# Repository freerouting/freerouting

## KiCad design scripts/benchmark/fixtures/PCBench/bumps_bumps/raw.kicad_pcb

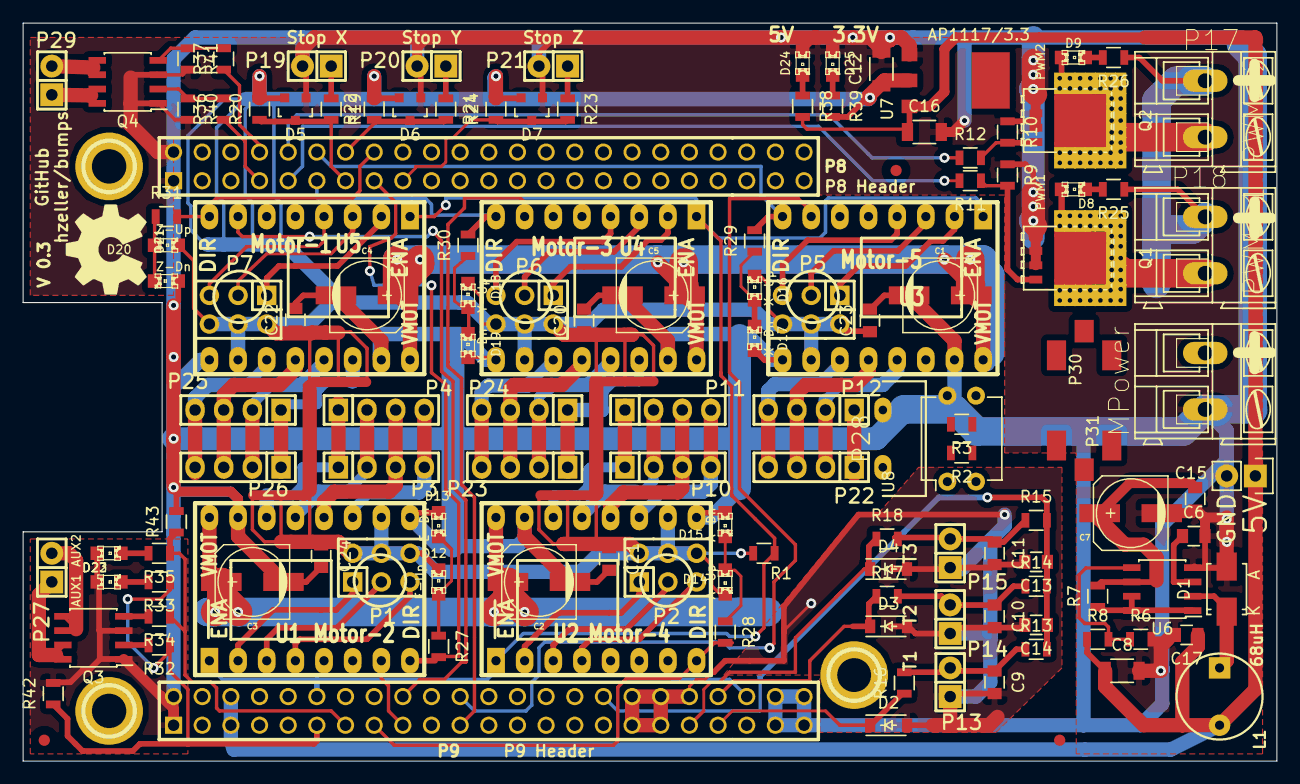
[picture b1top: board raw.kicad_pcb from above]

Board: 2 copper layers, 111.1 x 65.4 mm, 134 parts (0 on the bottom side), 101 nets.

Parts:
C1, C2, C3, C4, C5, C7: 100u; c_elec_6.3x7.7
C6: 110p; C_0805
C8: 100u; C_1206
C9, C10, C11, C14: 10u; C_0805
C12, C16: 22u; C_1206
C13, C15, C17, C20, C21, C22, C23, C24: 100n; C_0805
D1: STPS130A; Diode-SMA_Standard
D2, D3, D4: 1.8V; SOD-123
D5, D6, D7: BAT54S; SOT-23
D8: PWM1; LED-0805
D9: PWM2; LED-0805
D12: E-Up; LED-0805
D13: E-Dn; LED-0805
D14: A-Up; LED-0805
D15: A-Dn; LED-0805
D16: X-Up; LED-0805
D17: X-Dn; LED-0805
D18: Y-Up; LED-0805
D19: Y-Dn; LED-0805
D20: Z-Up; LED-0805
D21: Z-Dn; LED-0805
D22: AUX1; LED-0805
D23: AUX2; LED-0805
D24: 5V; LED-0805
D25: 3.3V; LED-0805
L1: 68uH; INDUCTOR_V
M1, M2, M3: CONN_1; 1pin
P1, P2, P5, P6, P7: DIL6; Pin_Header_Straight_2x03
P3, P4: Mot-E; Pin_Header_Straight_1x04
P8: P8 Header; PIN_ARRAY_23X2
P9: P9 Header; PIN_ARRAY_23X2
P10, P11: Mot-A; Pin_Header_Straight_1x04
P12, P22: Mot-X; Pin_Header_Straight_1x04
P13: T1; Pin_Header_Straight_1x02
P14: T2; Pin_Header_Straight_1x02
P15, P32: T3; Pin_Header_Straight_1x02
P16: MPower; AK300-2
P17: PWM-2; AK300-2
P18: PWM-1; AK300-2
P19: END-X; Pin_Header_Straight_1x02
P20: END-Y; Pin_Header_Straight_1x02
P21: END-Z; Pin_Header_Straight_1x02
P23, P24: Mot-Y; Pin_Header_Straight_1x04
P25, P26: Mot-Z; Pin_Header_Straight_1x04
P27: Aux; Pin_Header_Straight_1x02
P28: KillSwitch; WideHeader
P29: PWM; Pin_Header_Straight_1x02
P30, P31: CONN_01X01; FuseBlade
Q1, Q2: BUK9Y15-60E; SOT-669_LFPAK_ThermalVias-1
Q3, Q4: FDS9926A; SOIC-8_3.9x4.9mm_Pitch1.27mm
R1, R3, R13, R14, R15, R20, R22, R24: 4k7; R_0805
R2: 330; R_0805
R6, R27, R28, R29, R30, R31, R33, R35, R38, R39: 1k; R_0805
R7: 0R3; R_0805
R8: 3k; R_0805
R9, R10, R40, R41, R42, R43: 100k; R_0805
R11, R12, R16, R17, R18, R19, R21, R23, R32, R34, R36, R37: 68; R_0805
R25, R26: 2k2; R_0805
U1: Motor-2; POLOLU
U2: Motor-4; POLOLU
U3: Motor-5; POLOLU
U4: Motor-3; POLOLU
U5: Motor-1; POLOLU
U6: MC34063; SOIC-8_3.9x4.9mm_Pitch1.27mm
U7: AP1117/3.3; SOT-223-3
U8: PC817; DIP-4_W7.62mm

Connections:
AGND: C9.2, C10.2, C11.2, C13.2, C14.2, D2.2, D3.2, D4.2, P9.33, P9.34, P9.35, P9.36, P9.38, P13.1, P14.1, P15.1
AUX_1: P9.11, R32.1, R33.1, R42.1
AUX_2: P9.13, R34.1, R35.1, R43.1
DIR_A: P9.15, R28.2, U2.8
DIR_E: P8.15, R27.2, U1.8
DIR_X: P8.12, R29.2, U3.8
DIR_Y: P8.11, R30.2, U4.8
DIR_Z: P8.16, R31.2, U5.8
END_X: D5.3, P8.13, R19.2, R20.1
END_Y: D6.3, P8.14, R21.2, R22.1
END_Z: D7.3, P8.17, R23.2, R24.1
GND: C1.2, C2.2, C3.2, C4.2, C5.2, C6.2, C7.2, C8.2, C12.2, C15.2, C16.2, C17.2, C20.2, C21.2, C22.2, C23.2, C24.2, D1.2, D5.1, D6.1, D7.1, D13.1, D15.1, D17.1, D19.1, D21.1, D22.1, D23.1, D24.1, D25.1, P8.1, P8.2, P9.1, P9.2, P9.43, P9.44, P9.45, P9.46, P16.2, P19.2, P20.2, P21.2, P28.1, P32.2, Q1.1, Q1.2, Q1.3, Q2.1, Q2.2, Q2.3, Q3.1, Q3.3, Q4.1, Q4.3, R3.2, R6.2, R9.1, R10.1, R40.2, R41.2, R42.2, R43.2, U1.9, U1.15, U2.9, U2.15, U3.9, U3.15, U4.9, U4.15, U5.9, U5.15, U6.4, U7.1
unnamed: C6.1, U6.3
unnamed: C9.1, P13.2, R13.1, R16.2
unnamed: C10.1, P14.2, R14.1, R17.2
unnamed: C11.1, P15.2, R15.1, R18.2
unnamed: D1.1, L1.1, U6.2
unnamed: D8.1, P18.2, Q1.5
unnamed: D8.2, R25.2
unnamed: D9.1, P17.2, Q2.5
unnamed: D9.2, R26.2
unnamed: D12.1, D13.2, R27.1
unnamed: D14.1, D15.2, R28.1
unnamed: D16.1, D17.2, R29.1
unnamed: D18.1, D19.2, R30.1
unnamed: D20.1, D21.2, R31.1
unnamed: D22.2, R33.2
unnamed: D23.2, R35.2
unnamed: D24.2, R38.1
unnamed: D25.2, R39.1
unnamed: P1.1, U1.2
unnamed: P1.2, U1.3
unnamed: P1.3, U1.4
unnamed: P2.1, U2.2
unnamed: P2.2, U2.3
unnamed: P2.3, U2.4
unnamed: P3.1, P4.1, U1.14
unnamed: P3.2, P4.2, U1.13
unnamed: P3.3, P4.3, U1.12
unnamed: P3.4, P4.4, U1.11
unnamed: P5.1, U3.2
unnamed: P5.2, U3.3
unnamed: P5.3, U3.4
unnamed: P6.1, U4.2
unnamed: P6.2, U4.3
unnamed: P6.3, U4.4
unnamed: P7.1, U5.2
unnamed: P7.2, U5.3
unnamed: P7.3, U5.4
unnamed: P10.1, P11.1, U2.14
unnamed: P10.2, P11.2, U2.13
unnamed: P10.3, P11.3, U2.12
unnamed: P10.4, P11.4, U2.11
unnamed: P12.1, P22.1, U3.14
unnamed: P12.2, P22.2, U3.13
unnamed: P12.3, P22.3, U3.12
unnamed: P12.4, P22.4, U3.11
unnamed: P16.1, P30.1
unnamed: P19.1, R19.1
unnamed: P20.1, R21.1
unnamed: P21.1, R23.1
unnamed: P23.1, P24.1, U4.14
unnamed: P23.2, P24.2, U4.13
unnamed: P23.3, P24.3, U4.12
unnamed: P23.4, P24.4, U4.11
unnamed: P25.1, P26.1, U5.14
unnamed: P25.2, P26.2, U5.13
unnamed: P25.3, P26.3, U5.12
unnamed: P25.4, P26.4, U5.11
unnamed: P27.1, Q3.7, Q3.8
unnamed: P27.2, Q3.5, Q3.6
unnamed: P28.2, U8.2
unnamed: P29.1, Q4.7, Q4.8
unnamed: P29.2, Q4.5, Q4.6
unnamed: Q1.4, R9.2, R11.1
unnamed: Q2.4, R10.2, R12.2
unnamed: Q3.2, R32.2
unnamed: Q3.4, R34.2
unnamed: Q4.2, R36.2, R40.1
unnamed: Q4.4, R37.2, R41.1
unnamed: R2.2, U8.1
unnamed: R6.1, R8.2, U6.5
unnamed: R7.1, U6.1, U6.7, U6.8
PWM_1: P8.9, R11.2
PWM_2: P8.10, R12.1
PWM_3: P8.7, R36.1
PWM_4: P8.8, R37.1
STEP_A: P9.42, U2.7
STEP_E: P9.17, U1.7
STEP_X: P9.22, U3.7
STEP_Y: P9.21, U4.7
STEP_Z: P9.18, U5.7
TEMP_1: D2.1, P9.39, R16.1
TEMP_2: D3.1, P9.40, R17.1
TEMP_3: D4.1, P9.37, R18.1
VDD_3V3: C12.1, C20.1, C21.1, C22.1, C23.1, C24.1, D5.2, D6.2, D7.2, D12.2, D14.2, D16.2, D18.2, D20.2, P1.4, P1.5, P1.6, P2.4, P2.5, P2.6, P5.4, P5.5, P5.6, P6.4, P6.5, P6.6, P7.4, P7.5, P7.6, R1.2, R20.2, R22.2, R24.2, R39.2, U1.10, U2.10, U3.10, U4.10, U5.10, U7.2, U8.4
VDD_5V: C8.1, C16.1, C17.1, L1.2, P9.5, P9.6, P32.1, R2.1, R8.1, R38.2, U7.3
VDD_ADC: C13.1, C14.1, P9.32, R13.2, R14.2, R15.2
VMOT: C1.1, C2.1, C3.1, C4.1, C5.1, C7.1, C15.1, P17.1, P18.1, P31.1, R7.2, R25.1, R26.1, U1.16, U2.16, U3.16, U4.16, U5.16, U6.6
~EN: P9.12, R1.1, U1.1, U2.1, U3.1, U4.1, U5.1
~EStop: R3.1, U1.5, U2.5, U3.5, U4.5, U5.5, U8.3

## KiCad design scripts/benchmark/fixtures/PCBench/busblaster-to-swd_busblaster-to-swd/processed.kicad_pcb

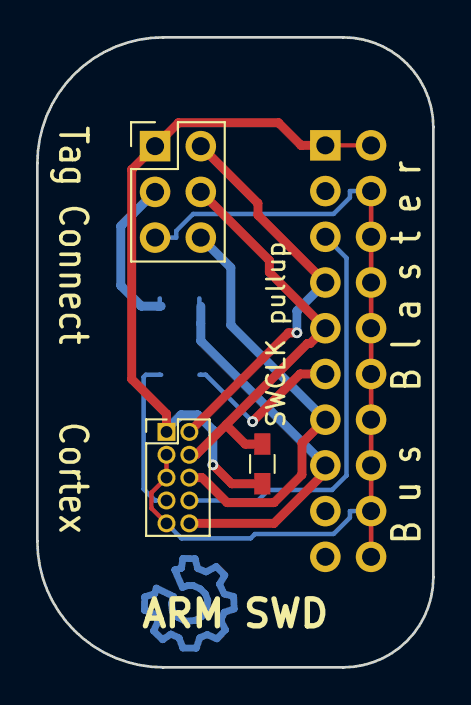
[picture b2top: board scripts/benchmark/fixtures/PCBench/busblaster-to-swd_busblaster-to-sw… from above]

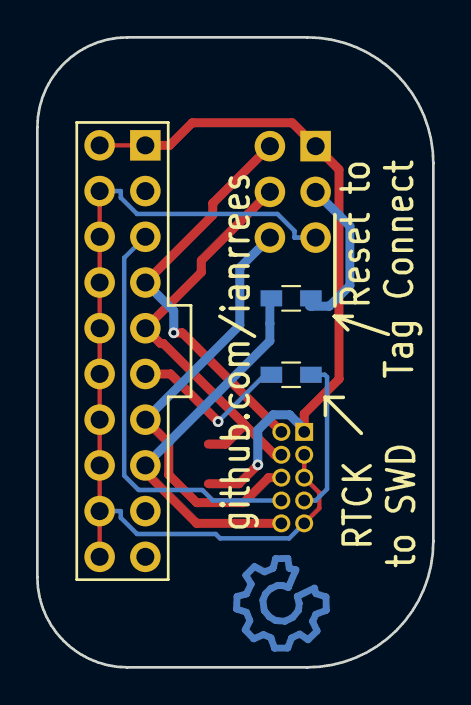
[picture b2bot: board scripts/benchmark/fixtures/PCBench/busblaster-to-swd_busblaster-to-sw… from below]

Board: 2 copper layers, 22.0 x 35.0 mm, 6 parts (2 on the bottom side), 10 nets.

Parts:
J101: CONN_02X10; Pin_Header_Straight_2x10_Pitch2.54mm
J102: Tag Connect; Pin_Header_Straight_2x03_Pitch2.54mm
J103: CONN_02X05; Pin_Header_Straight_2x05_Pitch1.27mm
JP101, JP102: Jumper_NC_Small; R_0603_HandSoldering
R101: 1k; R_0603_HandSoldering

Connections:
/GND: J101.4, J101.6, J101.8, J101.10, J101.12, J101.14, J101.16, J101.18, J101.20, J102.5, J103.3, J103.5, J103.9
/RTCK: J103.7, JP102.2
/SWO/TDO: J101.13, J102.6, J103.6
/TCK/SWCLK: J101.9, J102.4, J103.4, R101.2
/TDI: J101.5, J103.8
/TMS/SWDIO: J101.7, J102.2, J103.2
/Vtarget: J101.1, J101.2, J102.1, J103.1, R101.1
/~Reset: J102.3, JP101.1
unnamed: J101.11, JP102.1
unnamed: J101.15, J103.10, JP101.2

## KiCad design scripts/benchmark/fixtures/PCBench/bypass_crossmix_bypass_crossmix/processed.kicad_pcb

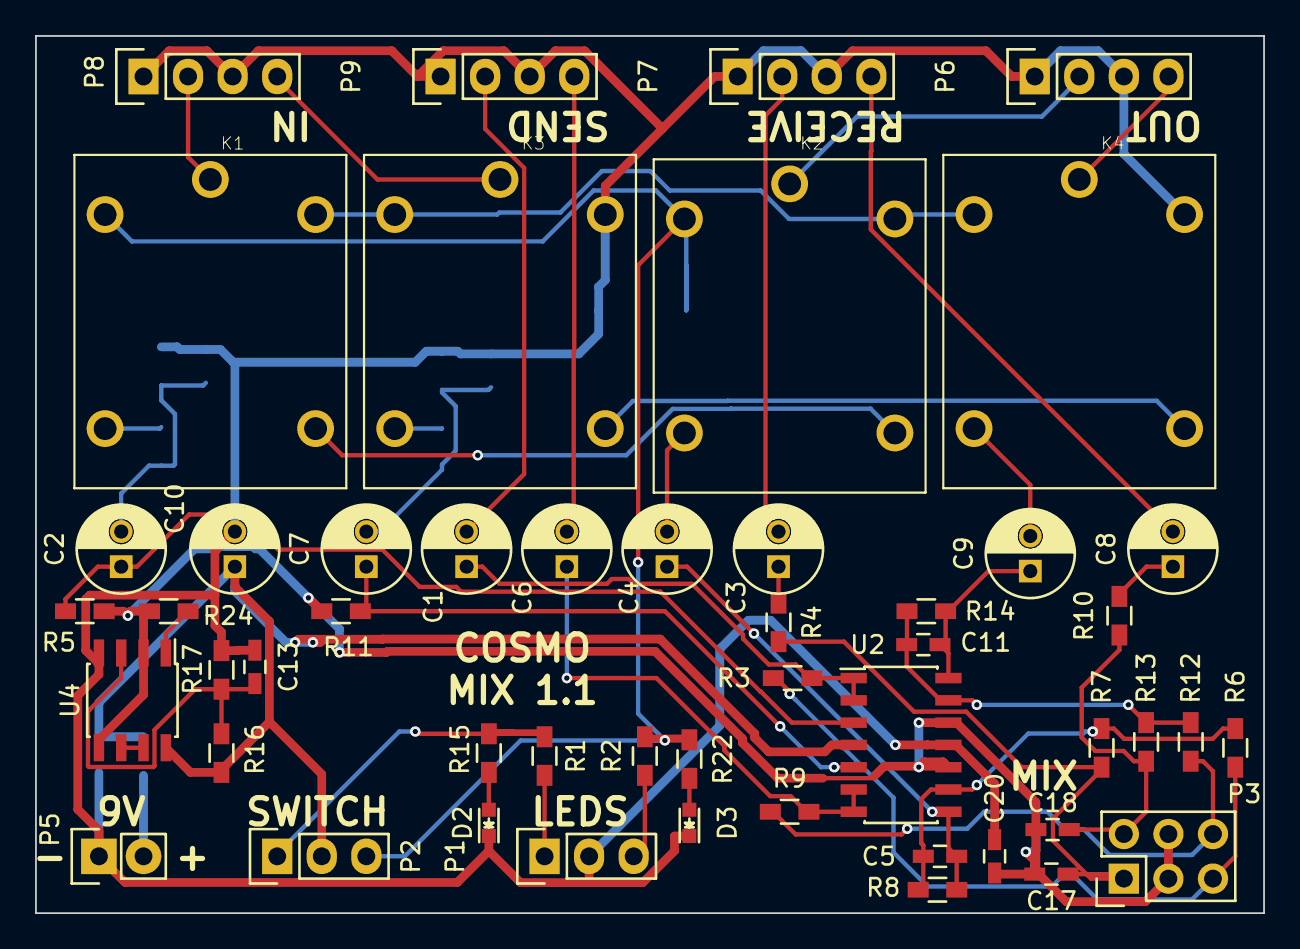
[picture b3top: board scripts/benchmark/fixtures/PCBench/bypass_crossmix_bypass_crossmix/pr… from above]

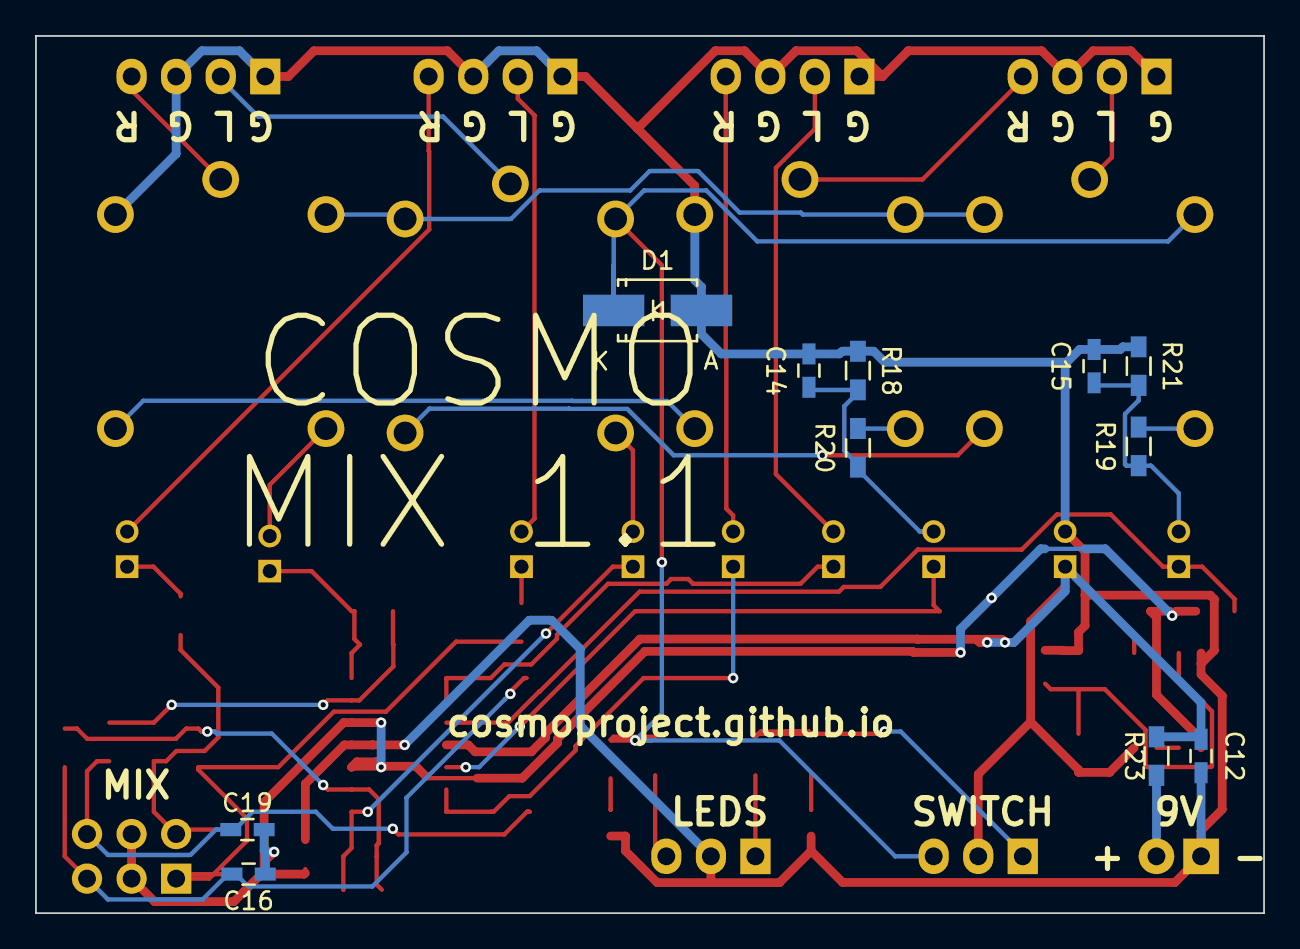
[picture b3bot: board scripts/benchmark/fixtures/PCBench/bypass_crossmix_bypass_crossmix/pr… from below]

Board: 2 copper layers, 70.0 x 50.0 mm, 61 parts (11 on the bottom side), 44 nets.

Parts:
C1, C2, C3, C4, C6, C7, C8, C9, C10: 100u; C_Radial_D5_L11_P2
C5, C11: C; C_0603_HandSoldering
C12, C13, C20: 100n; C_0603_HandSoldering
C14, C15: 10n; C_0603_HandSoldering
C16, C17, C18, C19: 100p; C_0603_HandSoldering
D1: D; SMA_Handsoldering
D2: RED; LED-0603
D3: GREEN; LED-0603
K1, K2, K3, K4: RELAY-HLS8L-DC5V-S-C(5P-19X15MM); REY5-19.0X15.0X15.0MM
P1: STATUS LED; Pin_Header_Straight_1x03
P2: SWITCH; Pin_Header_Straight_1x03
P3: DRYWET; Pin_Header_Straight_2x03
P5: 9V; Pin_Header_Straight_1x02
P6: OUT; Pin_Header_Straight_1x04
P7: RECEIVE; Pin_Header_Straight_1x04
P8: IN; Pin_Header_Straight_1x04
P9: SEND; Pin_Header_Straight_1x04
R1, R15: 180; R_0603_HandSoldering
R2, R22: 150; R_0603_HandSoldering
R3, R4, R6, R7, R9, R10, R12, R13, R16, R17: 47k; R_0603_HandSoldering
R5, R11, R18, R21: 1M; R_0603_HandSoldering
R8, R14: 100k; R_0603_HandSoldering
R19, R20: 470; R_0603_HandSoldering
R23, R24: 12; R_0603_HandSoldering
U2: TL074; SOIC-14_3.9x8.7mm_Pitch1.27mm
U4: LM358; SOIC-8_3.9x4.9mm_Pitch1.27mm

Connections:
+5V: C10.1, C12.1, P2.2, R16.1, R23.1, U2.4, U4.8
-5V: C10.2, C12.2, C13.1, C14.2, C15.2, C20.2, D1.2, D2.1, D3.1, K3.3, K4.3, P1.2, P5.1, P6.1, P6.3, P7.1, P7.3, P8.1, P8.3, P9.1, P9.3, R17.2, R18.1, R21.1, U2.11, U4.4
/in_left: K1.1, P8.2
/in_right: K3.1, P8.4
/out_left: K2.1, P6.2
/out_right: K4.1, P6.4
/receive_left: C3.2, P7.2
/receive_right: C8.2, P7.4
/send_left: C1.2, P9.2
/send_right: C6.2, P9.4
GND: C16.1, C17.2, C18.2, C19.1, C20.1, P3.3, P3.4, R5.2, R11.2, R24.1, U2.10, U2.12, U4.2, U4.5
unnamed: C1.1, R3.2, U2.1, U2.2
unnamed: C2.1, R5.1, U2.3
unnamed: C3.1, R4.1
unnamed: C4.1, C5.2, R8.2, U2.8
unnamed: C4.2, K2.4
unnamed: C5.1, R6.1, R7.1, R8.1, U2.9
unnamed: C6.1, R9.2, U2.6, U2.7
unnamed: C7.1, R11.1, U2.5
unnamed: C8.1, R10.1
unnamed: C9.2, K4.4
unnamed: C11.1, R12.1, R13.1, R14.1, U2.13
unnamed: C9.1, C11.2, R14.2, U2.14
unnamed: C13.2, R16.2, R17.1, U4.3
unnamed: C7.2, C14.1, R18.2, R20.1
unnamed: C2.2, C15.1, R19.1, R21.2
unnamed: C16.2, P3.5, R3.1, R6.2
unnamed: C17.1, P3.1, R4.2, R7.2
unnamed: C18.1, P3.2, R10.2, R13.2
unnamed: C19.2, P3.6, R9.1, R12.2
unnamed: D1.1, K1.2, K2.2, P2.3, R2.2, R22.1
unnamed: D2.2, R15.1
unnamed: D3.2, R22.2
unnamed: K1.3, K2.3, K3.2, K4.2
unnamed: K1.4, R19.2
unnamed: K1.5, K2.5
unnamed: K3.4, R20.2
unnamed: K3.5, K4.5
unnamed: P1.1, R1.1
unnamed: P1.3, R2.1
unnamed: P2.1, R1.2, R15.2
unnamed: P5.2, R23.2
unnamed: R24.2, U4.1
unnamed: U4.6, U4.7

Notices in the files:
scripts/benchmark/fixtures/PCBench/bumps_bumps/raw.kicad_pcb:
License: CC-BY-SA
